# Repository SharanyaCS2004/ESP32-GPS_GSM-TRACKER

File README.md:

# ESP32 GPS + GSM Tracker

A compact IoT tracking device based on an ESP32-WROOM-32, SIM800C cellular module, and u‑blox NEO‑M8N GPS. It features Li‑ion battery management (TP4056), a regulated 4 V rail (TPSM53602), and a 3.3 V supply (AMS1117) to power the ESP32.

---

## 🖼️ Preview

### 📐 Schematic

### 🧭 PCB Layout

### 🧱 3D Render

---

## 🚀 Features

- **GPS positioning** via NEO‑M8N (UART)  
- **GSM/GPRS connectivity** via SIM800C (UART)  
- Li‑ion **battery charging** with TP4056  
- Stable **4 V buck** for radio modules (TPSM53602)  
- **3.3 V regulator** for ESP32 logic (AMS1117)  
- Push‑buttons for user input (IO25/IO26)  
- Status LED indicators for power & network  
- 4‑layer PCB: Top & bottom for signals, inner planes for GND & 4 V

---

## 📂 Repository Structure
```
├── Gerber Files/ ← Manufacturing outputs
├── Images/
│ ├── 3D.png ← PCB 3D render
│ ├── CKT.png ← Final schematic
│ └── pcb_routing.png ← Routed PCB view
├── PROJECT FILES/
│ ├── ESP32 GPS + GSM Tracker.kicad_pro
│ ├── ESP32 GPS + GSM Tracker.kicad_sch
│ └── ESP32 GPS + GSM Tracker.kicad_pcb
├── README.md ← This file
```

---

## 🔧 Hardware Overview

| Module      | Part / Footprint                 | Capacitors            |
|-------------|----------------------------------|-----------------------|
| **ESP32**   | `Module:ESP32-WROOM-32`          | 0.1 µF + 10 µF on VDD  |
| **SIM800C** | `RF_Module:SIM800C`              | 0.1 µF + 100 µF on VBAT|
| **NEO‑M8N** | `RF_Module:UBlox_NEO-M8N`        | 0.1 µF + 1 µF on VCC   |
| **TP4056**  | `Package_SO:SOIC-8`               | 1 µF IN/1 µF OUT      |
| **TPSM53602**| `Texas:TPSM53602RDA`            | 10 µF IN/22 µF OUT    |
| **AMS1117** | `Package_TO_SOT_SMD:SOT-223`     | 10 µF IN/10 µF OUT    |

---

## 🔌 Pin Wiring Summary

- **SIM800C (U2)**  
  - VBAT → 4 V rail  
  - UART1_TXD → ESP32 IO16  
  - UART1_RXD ← ESP32 IO17 (via 1 k+2 k divider)  
- **NEO‑M8N (U3)**  
  - VCC → 4 V rail  
  - TX → ESP32 IO4  
  - RX ← ESP32 IO5  
- **ESP32 (U1)**  
  - VDD → 3.3 V regulator  
  - EN → 3.3 V via 10 kΩ pull‑up  
  - IO25, IO26 → SW1, SW2  
  - IO27 → Status LED  

---

## 🛠️ Build & PCB Layout

1. **Open KiCad project**:  
   ```bash
   cd "PROJECT FILES"
   kicad ESP32\ GPS\ +\ GSM\ Tracker.kicad_pro
   
2. Review ERC, assign footprints, then update PCB.

3. Fill zones:
   Layer 2 → GND
   Layer 3 → 4 V

4. Route critical nets on Top, overflow on Bottom.

5. Generate Gerbers via:
```File → Plot```  and  ```Fabrication Outputs → Generate Drill Files```

📋 License
This project is released under the MIT License.

Built by Sharanya — a portable, battery‑powered GPS/GSM tracker ready for IoT deployments!

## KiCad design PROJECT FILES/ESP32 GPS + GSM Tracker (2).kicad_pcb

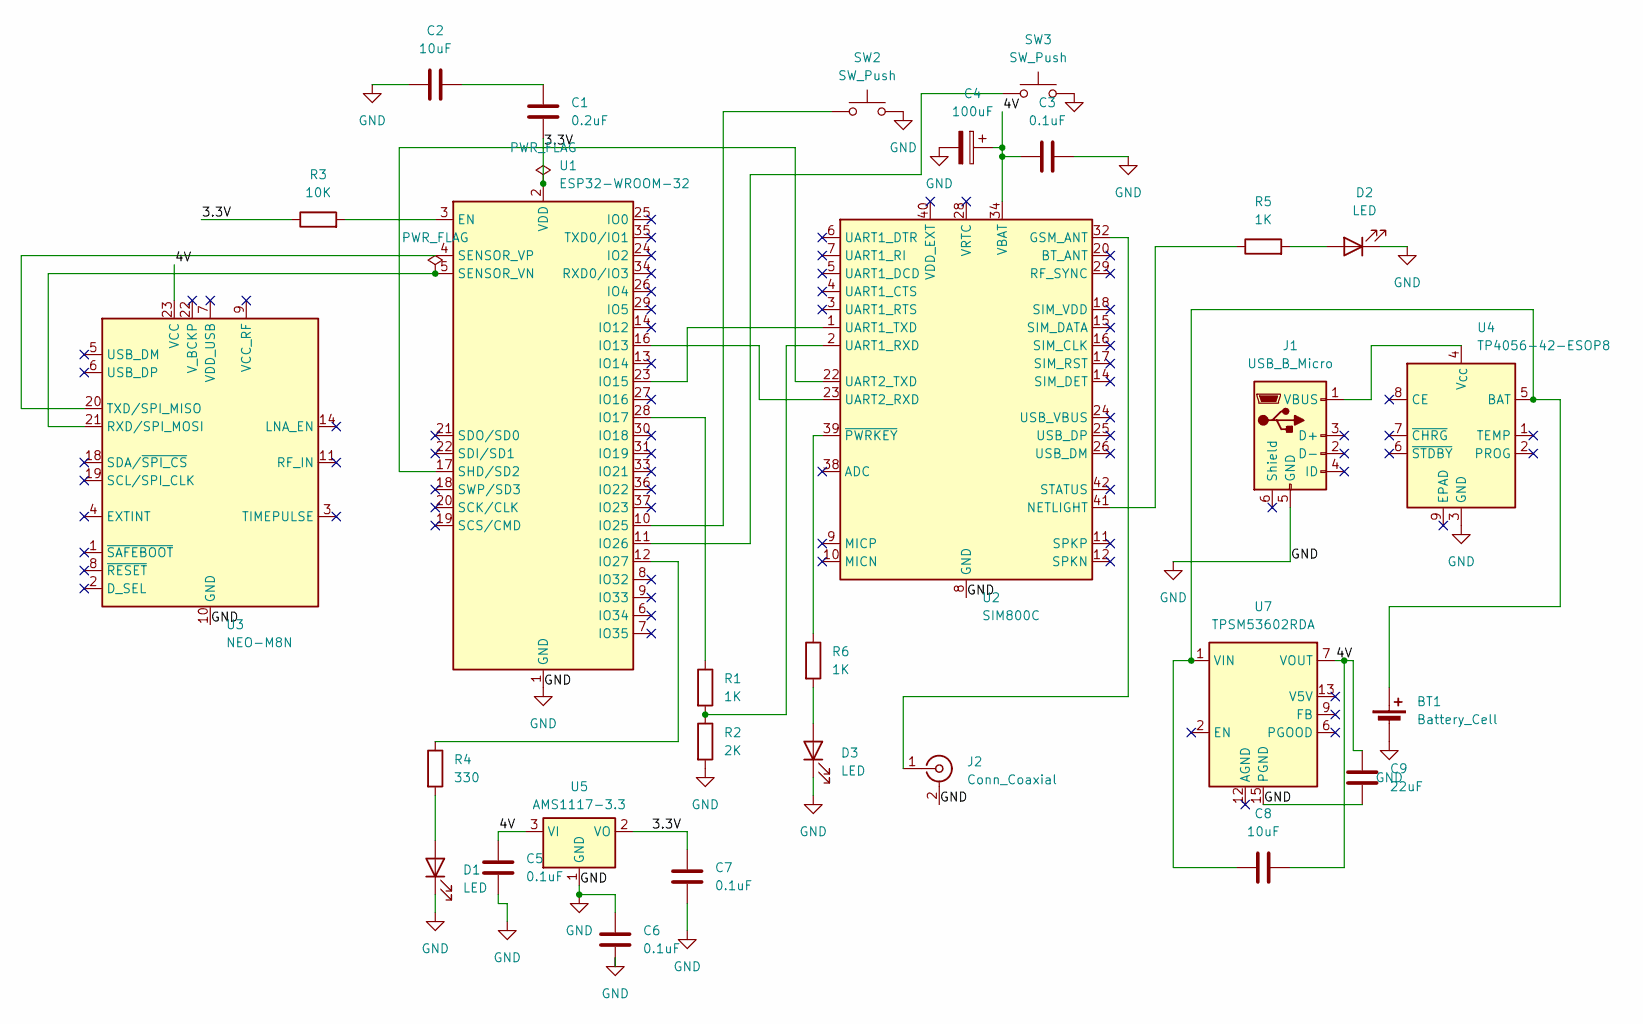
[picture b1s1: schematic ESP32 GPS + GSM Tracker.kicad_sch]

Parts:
BT1: Battery_Cell; BatteryHolder_Keystone_1042_1x18650
C1: 0.2uF; C_0603_1608Metric
C2, C8: 10uF; C_0603_1608Metric
C3, C5, C6, C7: 0.1uF; C_0603_1608Metric
C4: 100uF; C_0603_1608Metric
C9: 22uF; C_0603_1608Metric
D1, D2, D3: LED; LED_D5.0mm
J1: USB_B_Micro; USB_Micro-B_Molex-105133-0001
J2: Conn_Coaxial; SMA_Amphenol_132134-11_Vertical
R1, R5, R6: 1K; R_0603_1608Metric
R2: 2K; R_0603_1608Metric
R3: 10K; R_0603_1608Metric
R4: 330; R_0603_1608Metric
SW2, SW3: SW_Push; SW_PUSH_6mm
U1: ESP32-WROOM-32
U2: SIM800C; SIMCom_SIM800C
U3: NEO-M8N; ublox_NEO
U4: TP4056-42-ESOP8; SOIC-8-1EP_3.9x4.9mm_P1.27mm_EP2.41x3.3mm_ThermalVias
U5: AMS1117-3.3; SOT-223-3_TabPin2
U7: TPSM53602RDA; Texas_B3QFN-14-1EP_5x5.5mm_P0.65mm_ThermalVia

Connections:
/4V: C3.1, C4.1, C5.1, C8.2, C9.1, U2.34 (VBAT), U2.35 (VBAT), U3.23 (VCC), U5.3 (VI), U7.7 (VOUT), U7.8 (VOUT)
GND: BT1.2 (-), C2.1, C3.2, C4.2, C5.2, C6.1, C6.2, C7.2, C9.2, D1.1 (K), D2.1 (K), D3.1 (K), J1.5 (GND), J2.2 (Ext), R2.2, SW2.2, SW3.2, U1.1 (GND), U1.15 (GND), U1.38 (GND), U1.39 (GND), U2.8 (GND), U2.13 (GND), U2.19 (GND), U2.21 (GND), U2.27 (GND), U2.30 (GND), U2.31 (GND), U2.33 (GND), U2.36 (GND), U2.37 (GND), U3.10 (GND), U3.12 (GND), U3.13 (GND), U3.24 (GND), U4.3 (GND), U5.1 (GND), U7.3 (PGND), U7.10 (PGND), U7.11 (PGND), U7.15 (PGND)
unnamed: BT1.1 (+), C8.1, U4.5 (BAT), U7.1 (VIN), U7.14 (VIN)
unnamed: C1.1, C2.2
unnamed: D1.2 (A), R4.2
unnamed: D2.2 (A), R5.2
unnamed: D3.2 (A), R6.2
unnamed: J1.1 (VBUS), U4.4 (V_{CC})
unnamed: J2.1 (In), U2.32 (GSM_ANT)
unnamed: R3.2, U1.3 (EN)
unnamed: U1.16 (IO13), U2.23 (UART2_RXD)
unnamed: U1.23 (IO15), U2.1 (UART1_TXD)
unnamed: R1.1, U1.28 (IO17)
unnamed: SW2.1, U1.10 (IO25)
unnamed: SW3.1, U1.11 (IO26)
unnamed: R4.1, U1.12 (IO27)
unnamed: U1.5 (SENSOR_VN), U3.21 (RXD/SPI_MOSI)
unnamed: U1.4 (SENSOR_VP), U3.20 (TXD/SPI_MISO)
unnamed: R5.1, U2.41 (NETLIGHT)
unnamed: R1.2, R2.1, U2.2 (UART1_RXD)
unnamed: R6.1, U2.39 (~PWRKEY)

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
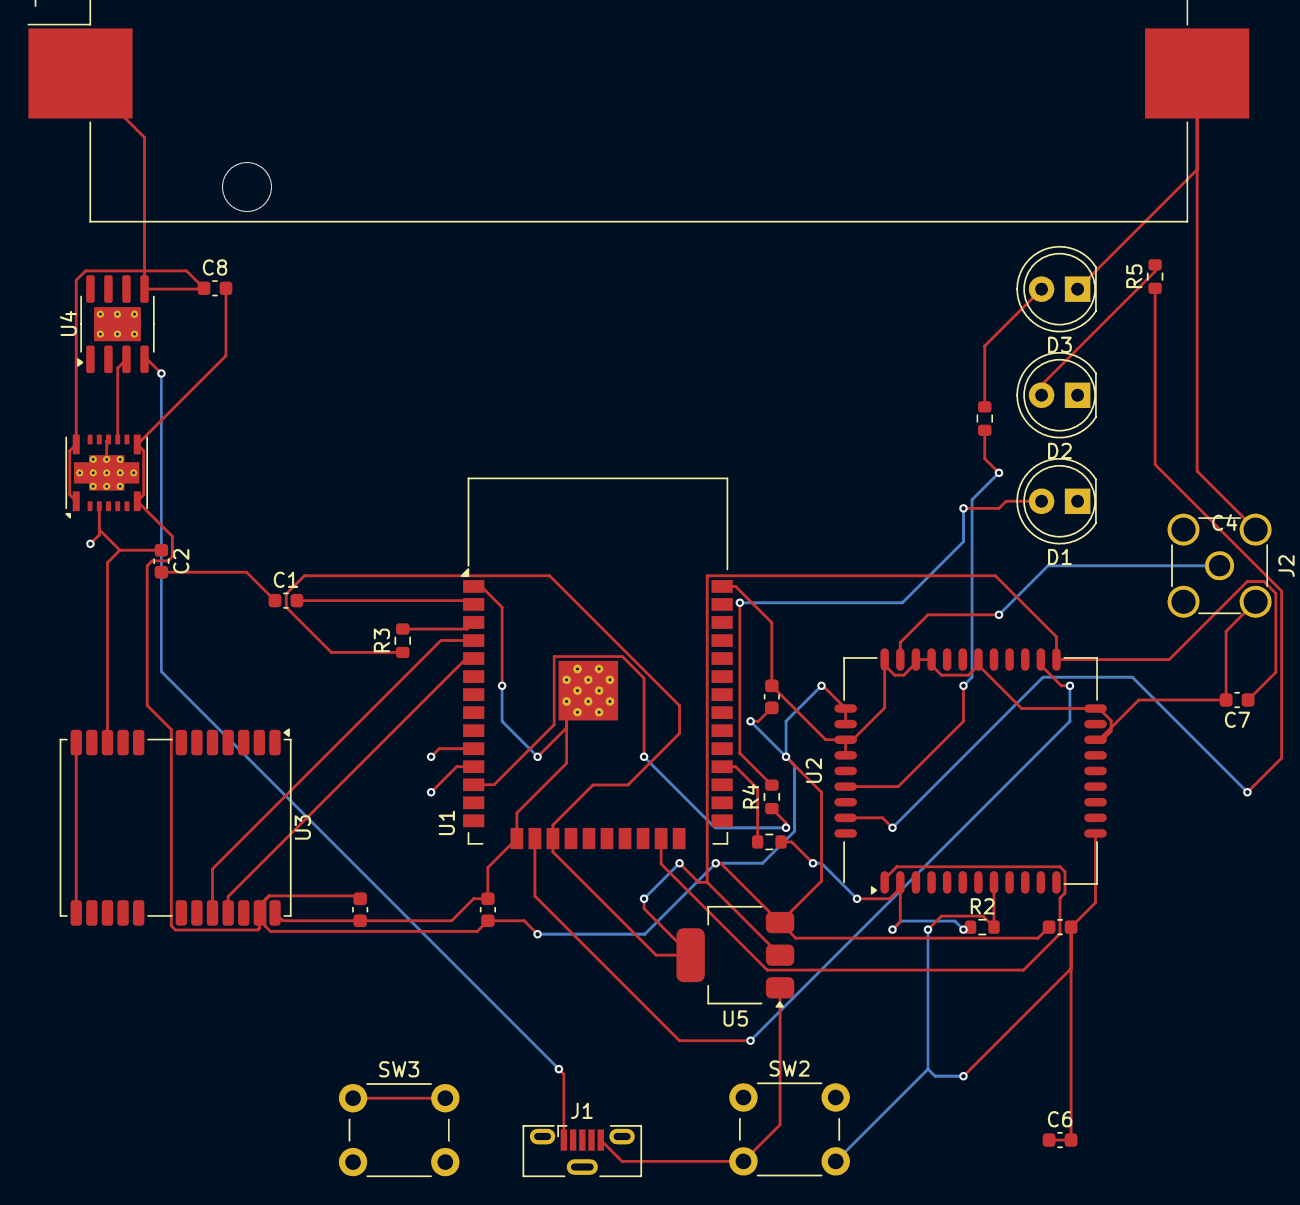
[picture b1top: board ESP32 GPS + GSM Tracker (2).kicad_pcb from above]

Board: 4 copper layers, 29 parts (0 on the bottom side), 23 nets.

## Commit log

2025-07-02 Rename pcb routing.png to pcb_routing.png
